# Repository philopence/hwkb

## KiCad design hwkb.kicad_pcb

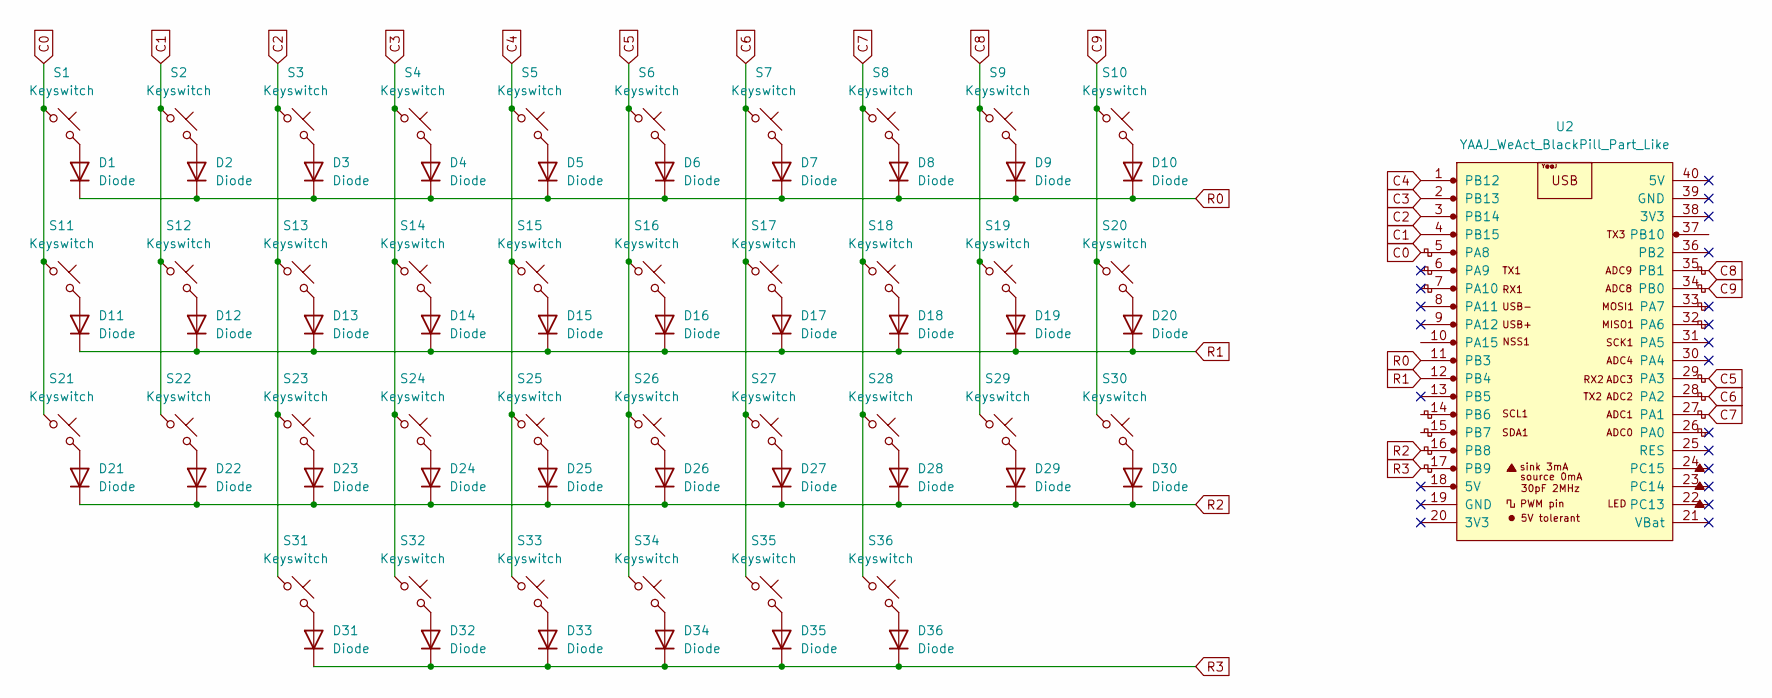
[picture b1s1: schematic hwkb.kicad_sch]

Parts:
D1, D2, D3, D4, D5, D6, D7, D8, D9, D10, D11, D12, D13, D14, D15, D16, D17, D18, D19, D20, D21, D22, D23, D24, D25, D26, D27, D28, D29, D30, D31, D32, D33, D34, D35, D36: Diode; Diode_DO-35
S1, S2, S3, S4, S5, S6, S7, S8, S9, S10, S11, S12, S13, S14, S15, S16, S17, S18, S19, S20, S21, S22, S23, S24, S25, S26, S27, S28, S29, S30, S31, S32, S33, S34, S35, S36: Keyswitch; MX_PCB_1.00u
U2: YAAJ_WeAct_BlackPill_Part_Like; YAAJ_WeAct_BlackPill_2

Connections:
C0: S1.1, S11.1, S21.1, U2.5 (PA8)
C1: S2.1, S12.1, S22.1, U2.4 (PB15)
C2: S3.1, S13.1, S23.1, S31.1, U2.3 (PB14)
C3: S4.1, S14.1, S24.1, S32.1, U2.2 (PB13)
C4: S5.1, S15.1, S25.1, S33.1, U2.1 (PB12)
C5: S6.1, S16.1, S26.1, S34.1, U2.29 (PA3)
C6: S7.1, S17.1, S27.1, S35.1, U2.28 (PA2)
C7: S8.1, S18.1, S28.1, S36.1, U2.27 (PA1)
C8: S9.1, S19.1, S29.1, U2.35 (PB1)
C9: S10.1, S20.1, S30.1, U2.34 (PB0)
unnamed: D1.2 (A), S1.2
unnamed: D2.2 (A), S2.2
unnamed: D3.2 (A), S3.2
unnamed: D4.2 (A), S4.2
unnamed: D5.2 (A), S5.2
unnamed: D6.2 (A), S6.2
unnamed: D7.2 (A), S7.2
unnamed: D8.2 (A), S8.2
unnamed: D9.2 (A), S9.2
unnamed: D10.2 (A), S10.2
unnamed: D11.2 (A), S11.2
unnamed: D12.2 (A), S12.2
unnamed: D13.2 (A), S13.2
unnamed: D14.2 (A), S14.2
unnamed: D15.2 (A), S15.2
unnamed: D16.2 (A), S16.2
unnamed: D17.2 (A), S17.2
unnamed: D18.2 (A), S18.2
unnamed: D19.2 (A), S19.2
unnamed: D20.2 (A), S20.2
unnamed: D21.2 (A), S21.2
unnamed: D22.2 (A), S22.2
unnamed: D23.2 (A), S23.2
unnamed: D24.2 (A), S24.2
unnamed: D25.2 (A), S25.2
unnamed: D26.2 (A), S26.2
unnamed: D27.2 (A), S27.2
unnamed: D28.2 (A), S28.2
unnamed: D29.2 (A), S29.2
unnamed: D30.2 (A), S30.2
unnamed: D31.2 (A), S31.2
unnamed: D32.2 (A), S32.2
unnamed: D33.2 (A), S33.2
unnamed: D34.2 (A), S34.2
unnamed: D35.2 (A), S35.2
unnamed: D36.2 (A), S36.2
R0: D1.1 (K), D2.1 (K), D3.1 (K), D4.1 (K), D5.1 (K), D6.1 (K), D7.1 (K), D8.1 (K), D9.1 (K), D10.1 (K), U2.11 (PB3)
R1: D11.1 (K), D12.1 (K), D13.1 (K), D14.1 (K), D15.1 (K), D16.1 (K), D17.1 (K), D18.1 (K), D19.1 (K), D20.1 (K), U2.12 (PB4)
R2: D21.1 (K), D22.1 (K), D23.1 (K), D24.1 (K), D25.1 (K), D26.1 (K), D27.1 (K), D28.1 (K), D29.1 (K), D30.1 (K), U2.16 (PB8)
R3: D31.1 (K), D32.1 (K), D33.1 (K), D34.1 (K), D35.1 (K), D36.1 (K), U2.17 (PB9)

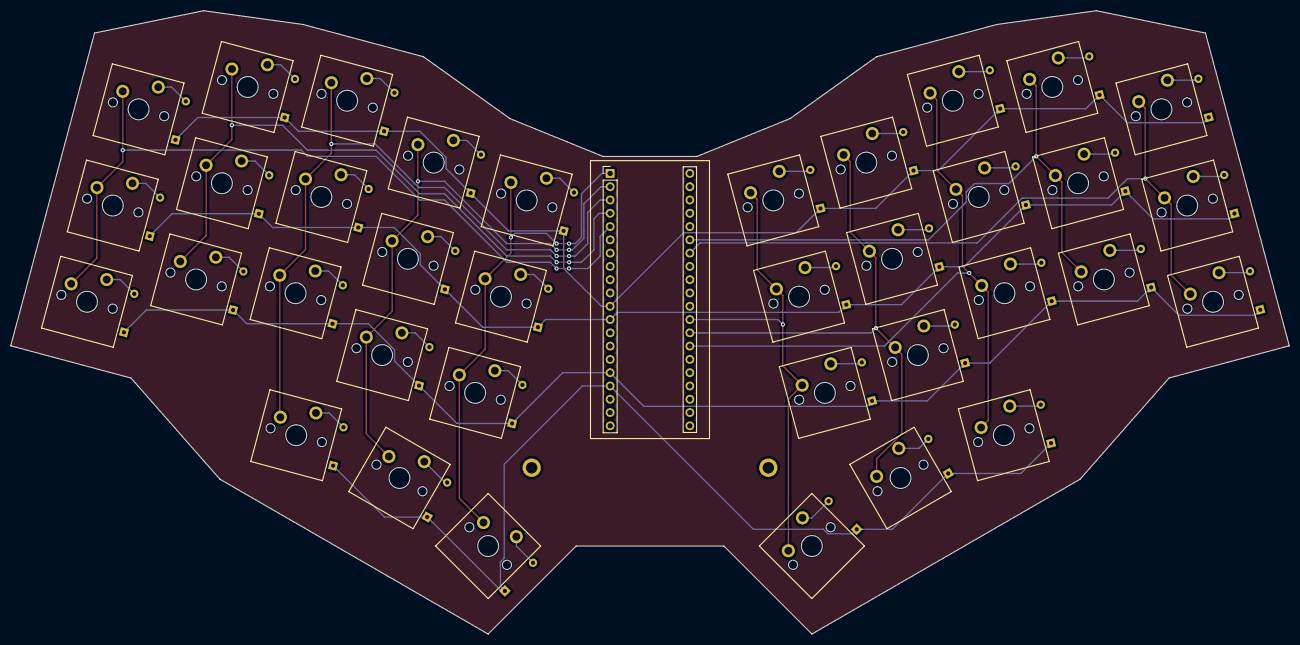
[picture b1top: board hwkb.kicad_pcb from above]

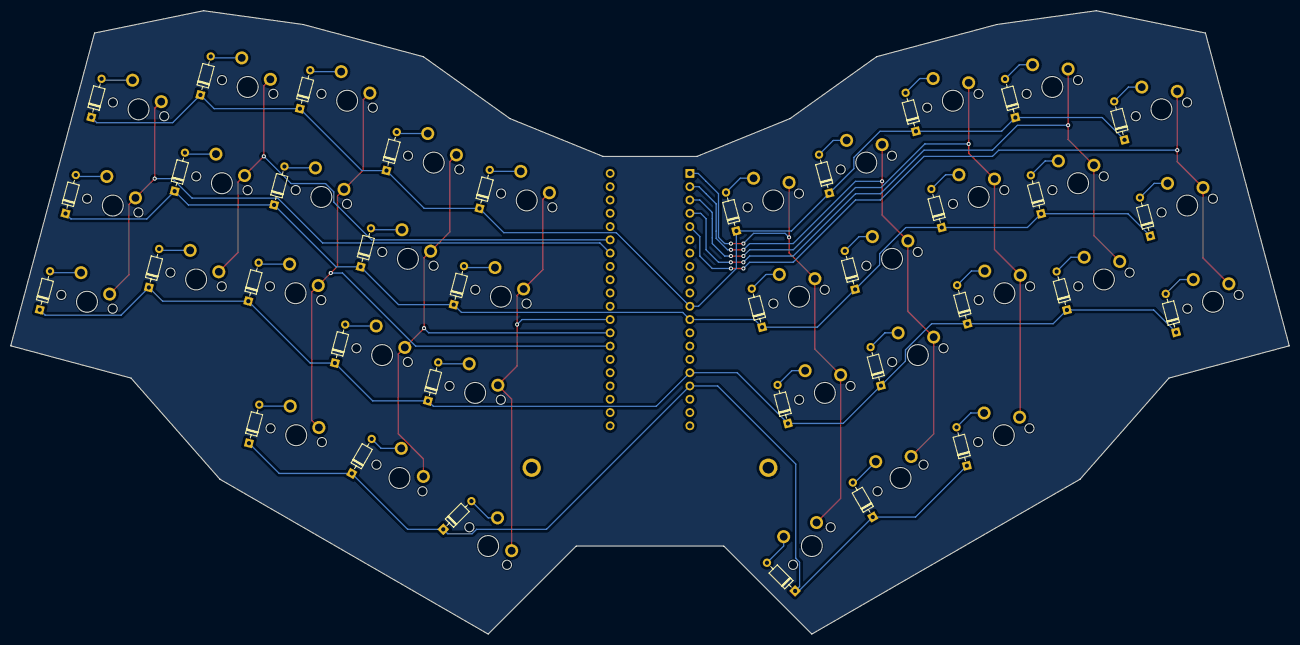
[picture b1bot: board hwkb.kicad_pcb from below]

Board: 2 copper layers, 244.5 x 119.2 mm, 73 parts (36 on the bottom side), 50 nets.

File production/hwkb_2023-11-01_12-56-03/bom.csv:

Designator,Footprint,Quantity,Value,LCSC Part #
"D1, D10, D11, D12, D13, D14, D15, D16, D17, D18, D19, D2, D20, D21, D22, D23, D24, D25, D26, D27, D28, D29, D3, D30, D31, D32, D33, D34, D35, D36, D4, D5, D6, D7, D8, D9",Diode_DO-35,36,Diode,
"S1, S10, S11, S12, S13, S14, S15, S16, S17, S18, S19, S2, S20, S21, S22, S23, S24, S25, S26, S27, S28, S29, S3, S30, S31, S32, S33, S34, S35, S36, S4, S5, S6, S7, S8, S9",MX_PCB_1.00u,36,Keyswitch,
U2,YAAJ_WeAct_BlackPill_2,1,YAAJ_WeAct_BlackPill_Part_Like,

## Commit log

2023-12-22 Fri Dec 22 12:27:58 PM CST 2023
2024-02-16 Fri Feb 16 04:01:31 PM CST 2024
